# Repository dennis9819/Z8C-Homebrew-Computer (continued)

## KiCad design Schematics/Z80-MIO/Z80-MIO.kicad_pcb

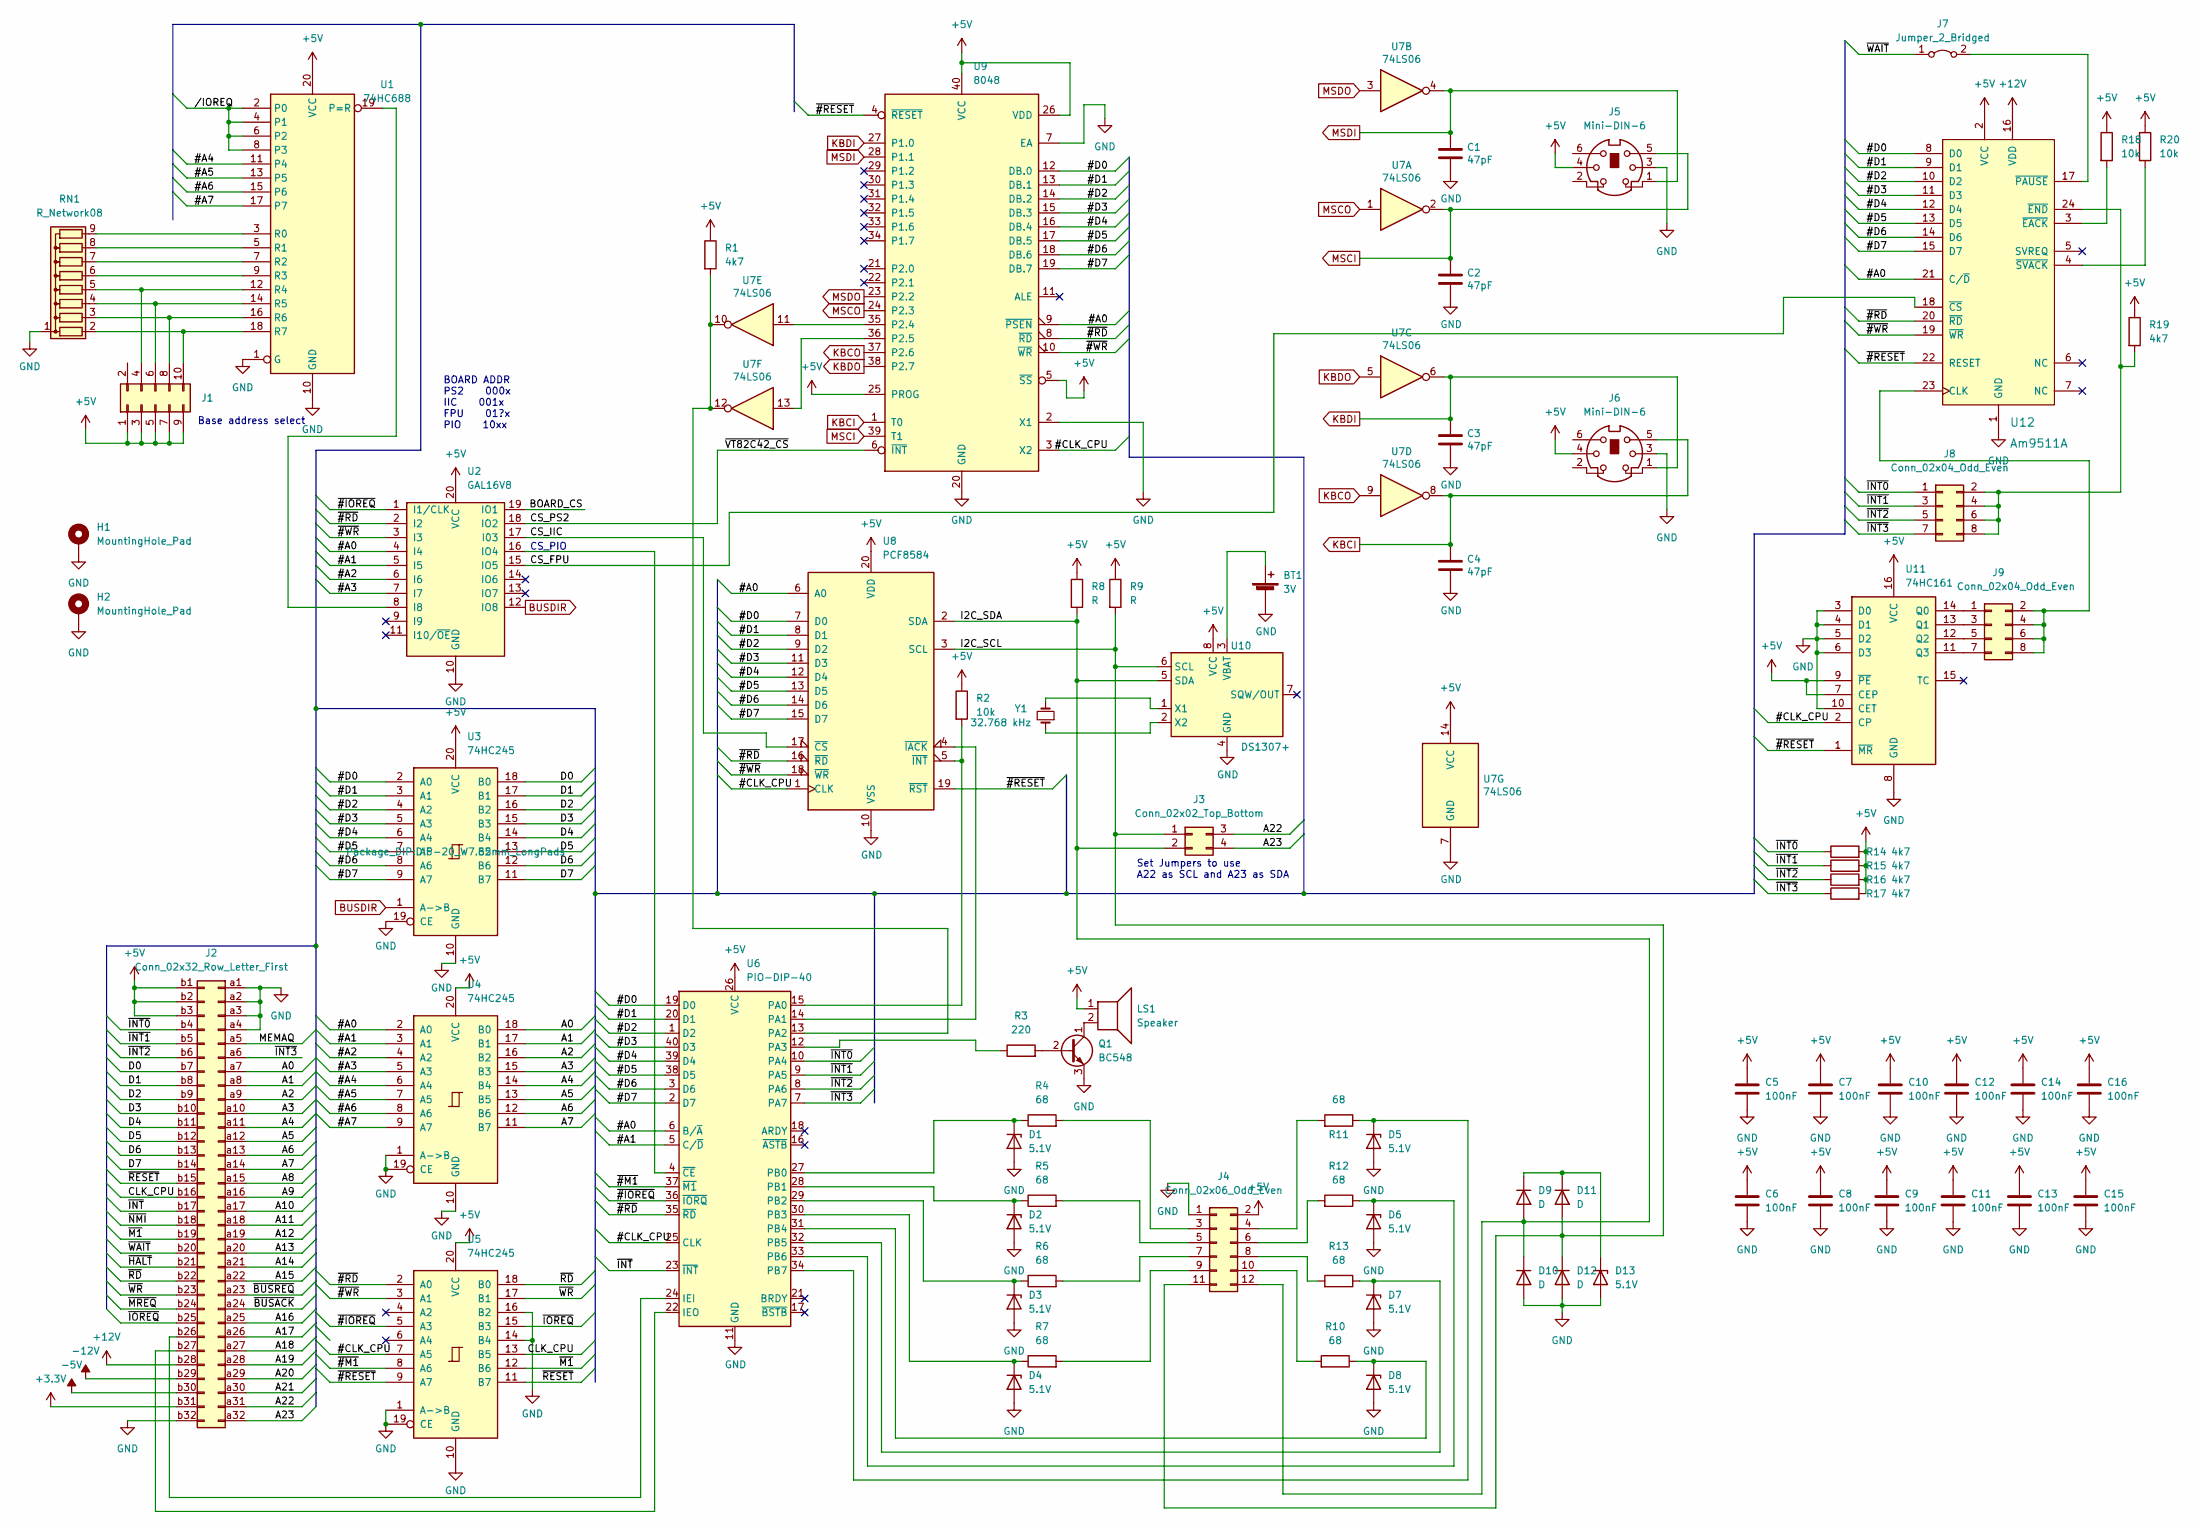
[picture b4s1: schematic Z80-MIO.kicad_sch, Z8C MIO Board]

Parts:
BT1: 3V; Battery_Holder_Coin_2032_BS-7
C1, C2, C3, C4: 47pF; C_Disc_D3.0mm_W2.0mm_P2.50mm
C5, C6, C7, C8, C9, C10, C11, C12, C13, C14, C15, C16: 100nF; C_Disc_D4.3mm_W1.9mm_P5.00mm
D1, D2, D3, D4, D5, D6, D7, D8, D13: 5.1V; D_DO-34_SOD68_P7.62mm_Horizontal
D9, D10, D11, D12: D; D_DO-34_SOD68_P7.62mm_Horizontal
H1, H2: MountingHole_Pad; MountingHole_3.2mm_M3_DIN965_Pad
J1: Conn_02x05_Odd_Even; PinHeader_2x05_P2.54mm_Vertical
J2: Conn_02x32_Row_Letter_First; DIN41612_Q_2x32_Male_Horizontal_THT
J3: Conn_02x02_Top_Bottom; PinHeader_2x02_P2.54mm_Vertical
J4: Conn_02x06_Odd_Even; IDC-Header_2x06_P2.54mm_Latch_Horizontal
J5, J6: Mini-DIN-6; PS2
J7: Jumper_2_Bridged; PinHeader_1x02_P2.54mm_Vertical
J8, J9: Conn_02x04_Odd_Even; PinHeader_2x04_P2.54mm_Vertical
LS1: Speaker; Piezo_Transducer_THT_PS1240P02BT
Q1: BC548; TO-92_Inline
R1, R14, R15, R16, R17, R19: 4k7; R_Axial_DIN0204_L3.6mm_D1.6mm_P7.62mm_Horizontal
R2, R18, R20: 10k; R_Axial_DIN0204_L3.6mm_D1.6mm_P7.62mm_Horizontal
R3: 220; R_Axial_DIN0204_L3.6mm_D1.6mm_P7.62mm_Horizontal
R4, R5, R6, R7, R10, R11, R12, R13: 68; R_Axial_DIN0204_L3.6mm_D1.6mm_P7.62mm_Horizontal
R8, R9: R; R_Axial_DIN0204_L3.6mm_D1.6mm_P7.62mm_Horizontal
RN1: R_Network08; R_Array_SIP9
U1: 74HC688; DIP-20_W7.62mm_LongPads
U2: GAL16V8; DIP-20_W7.62mm_LongPads
U3, U4, U5: 74HC245; DIP-20_W7.62mm_LongPads
U6: PIO-DIP-40; DIP-40_W15.24mm
U7: 74LS06; DIP-14_W7.62mm_Socket
U8: PCF8584; DIP-20_W7.62mm_LongPads
U9: 8048; DIP-40_W15.24mm_LongPads
U10: DS1307+; DIP-8_W7.62mm
U11: 74HC161; DIP-16_W7.62mm_LongPads
U12: Am9511A; DIP-24_W15.24mm_LongPads
Y1: 32.768 kHz; Crystal_AT310_D3.0mm_L10.0mm_Horizontal

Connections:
+3V3: J2.b31
+5V: C5.1, C6.1, C7.1, C8.1, C9.1, C10.1, C11.1, C12.1, C13.1, C14.1, C15.1, C16.1, J1.1, J1.3, J1.5, J1.7, J1.9, J2.b1, J2.b2, J2.b3, J4.2, J5.4, J6.4, LS1.1, R1.1, R2.1, R8.1, R9.1, R14.2, R15.2, R16.2, R17.2, R18.1, R19.1, R20.1, U1.20 (VCC), U2.20 (VCC), U3.20 (VCC), U4.20 (VCC), U5.20 (VCC), U6.26 (VCC), U7.14 (VCC), U8.20 (VDD), U9.5 (~SS), U9.25 (PROG), U9.26 (VDD), U9.40 (VCC), U10.8 (VCC), U11.7 (CEP), U11.9 (~PE), U11.16 (VCC), U12.2 (VCC)
+12V: J2.b28, U12.16 (VDD)
-5V: J2.b30
-12V: J2.b29
/#A0: U2.4 (I4), U4.2 (A0), U6.6 (B/~A), U8.6 (A0), U9.9 (~PSEN), U12.21 (C/~D)
/#A1: U2.5 (I5), U4.3 (A1), U6.5 (C/~D)
/#A2: U2.6 (I6), U4.4 (A2)
/#A3: U2.7 (I7), U4.5 (A3)
/#A4: U1.11 (P4), U4.6 (A4)
/#A5: U1.13 (P5), U4.7 (A5)
/#A6: U1.15 (P6), U4.8 (A6)
/#A7: U1.17 (P7), U4.9 (A7)
/#CLK_CPU: U5.7 (A5), U6.25 (CLK), U8.1 (CLK), U9.3 (X2), U11.2 (CP)
/#D0: U3.2 (A0), U6.19 (D0), U8.7 (D0), U9.12 (DB.0), U12.8 (D0)
/#D1: U3.3 (A1), U6.20 (D1), U8.8 (D1), U9.13 (DB.1), U12.9 (D1)
/#D2: U3.4 (A2), U6.1 (D2), U8.9 (D2), U9.14 (DB.2), U12.10 (D2)
/#D3: U3.5 (A3), U6.40 (D3), U8.11 (D3), U9.15 (DB.3), U12.11 (D3)
/#D4: U3.6 (A4), U6.39 (D4), U8.12 (D4), U9.16 (DB.4), U12.12 (D4)
/#D5: U3.7 (A5), U6.38 (D5), U8.13 (D5), U9.17 (DB.5), U12.13 (D5)
/#D6: U3.8 (A6), U6.3 (D6), U8.14 (D6), U9.18 (DB.6), U12.14 (D6)
/#D7: U3.9 (A7), U6.2 (D7), U8.15 (D7), U9.19 (DB.7), U12.15 (D7)
/A0: J2.a7, U4.18 (B0)
/A1: J2.a8, U4.17 (B1)
/A2: J2.a9, U4.16 (B2)
/A3: J2.a10, U4.15 (B3)
/A4: J2.a11, U4.14 (B4)
/A5: J2.a12, U4.13 (B5)
/A6: J2.a13, U4.12 (B6)
/A7: J2.a14, U4.11 (B7)
/A8: J2.a15
/A9: J2.a16
/A10: J2.a17
/A11: J2.a18
/A12: J2.a19
/A13: J2.a20
/A14: J2.a21
/A15: J2.a22
/A16: J2.a25
/A17: J2.a26
/A18: J2.a27
/A19: J2.a28
/A20: J2.a29
/A21: J2.a30
/A22: J2.a31, J3.3
/A23: J2.a32, J3.4
/BOARD_CS: U2.19 (IO1)
/CLK_CPU: J2.b16, U5.13 (B5)
/CS_FPU: U2.15 (IO5), U12.18 (~CS)
/CS_IIC: U2.17 (I03), U8.17 (~CS)
/CS_PS2: U2.18 (IO2), U9.6 (~INT)
/D0: J2.b7, U3.18 (B0)
/D1: J2.b8, U3.17 (B1)
/D2: J2.b9, U3.16 (B2)
/D3: J2.b10, U3.15 (B3)
/D4: J2.b11, U3.14 (B4)
/D5: J2.b12, U3.13 (B5)
/D6: J2.b13, U3.12 (B6)
/D7: J2.b14, U3.11 (B7)
/I2C_SCL: D11.2 (A), D12.1 (K), J3.1, J4.11, R9.2, U8.3 (SCL), U10.6 (SCL)
/I2C_SDA: D9.2 (A), D10.1 (K), J3.2, J4.12, R8.2, U8.2 (SDA), U10.5 (SDA)
/MEMAQ: J2.a5
//IOREQ: U1.2 (P0), U1.4 (P1), U1.6 (P2), U1.8 (P3)
/~#IOREQ: U2.1 (I1/CLK), U5.5 (A3), U6.36 (~IORQ)
/~#M1: U5.8 (A6), U6.37 (~M1)
/~#RD: U2.2 (I2), U5.2 (A0), U6.35 (~RD), U8.16 (~RD), U9.8 (~RD), U12.20 (~RD)
/~#RESET: U5.9 (A7), U8.19 (~RST), U9.4 (~RESET), U11.1 (~MR), U12.22 (RESET)
/~#WR: U2.3 (I3), U5.3 (A1), U8.18 (~WR), U9.10 (~WR), U12.19 (~WR)
/~BUSACK: J2.a24
/~BUSREQ: J2.a23
/~HALT: J2.b21
/~INT0: J2.b4, J8.1, R14.1, U6.10 (PA4)
/~INT1: J2.b5, J8.3, R15.1, U6.9 (PA5)
/~INT2: J2.b6, J8.5, R16.1, U6.8 (PA6)
/~INT3: J2.a6, J8.7, R17.1, U6.7 (PA7)
/~INT: J2.b17, U6.23 (~INT)
/~IOREQ: J2.b25, U5.15 (B3)
/~M1: J2.b19, U5.12 (B6)
/~MREQ: J2.b24
/~NMI: J2.b18
/~RD: J2.b22, U5.18 (B0)
/~RESET: J2.b15, U5.11 (B7)
/~WAIT: J2.b20, J7.1 (A)
/~WR: J2.b23, U5.17 (B1)
BUSDIR: U2.12 (IO8), U3.1 (A->B)
GND: BT1.neg, C1.2, C2.2, C3.2, C4.2, C5.2, C6.2, C7.2, C8.2, C9.2, C10.2, C11.2, C12.2, C13.2, C14.2, C15.2, C16.2, D1.2 (A), D2.2 (A), D3.2 (A), D4.2 (A), D5.2 (A), D6.2 (A), D7.2 (A), D8.2 (A), D10.2 (A), D12.2 (A), D13.2 (A), H1.1, H2.1, J2.a1, J2.a2, J2.a3, J2.a4, J2.b32, J4.1, J5.3, J6.3, Q1.3 (E), RN1.1 (common), U1.1 (G), U1.10 (GND), U2.10 (GND), U3.10 (GND), U3.19 (CE), U4.1 (A->B), U4.10 (GND), U4.19 (CE), U5.1 (A->B), U5.10 (GND), U5.14 (B4), U5.16 (B2), U5.19 (CE), U6.11 (GND), U7.7 (GND), U8.10 (VSS), U9.2 (X1), U9.7 (EA), U9.20 (GND), U10.4 (GND), U11.3 (D0), U11.4 (D1), U11.5 (D2), U11.6 (D3), U11.8 (GND), U11.10 (CET), U12.1 (GND)
KBCI: C4.1, J6.5, U7.8, U9.1 (T0)
KBCO: U7.9, U9.37 (P2.6)
KBDI: C3.1, J6.1, U7.6, U9.27 (P1.0)
KBDO: U7.5, U9.38 (P2.7)
MSCI: C2.1, J5.5, U7.2, U9.39 (T1)
MSCO: U7.1, U9.24 (P2.3)
MSDI: C1.1, J5.1, U7.4, U9.28 (P1.1)
MSDO: U7.3, U9.23 (P2.2)
unnamed: BT1.pos, U10.3 (VBAT)
unnamed: D1.1 (K), R4.1, U6.27 (PB0)
unnamed: D2.1 (K), R5.1, U6.28 (PB1)
unnamed: D3.1 (K), R6.1, U6.29 (PB2)
unnamed: D4.1 (K), R7.1, U6.30 (PB3)
unnamed: D5.1 (K), R11.1, U6.34 (PB7)
unnamed: D6.1 (K), R12.1, U6.33 (PB6)
unnamed: D7.1 (K), R13.1, U6.32 (PB5)
unnamed: D8.1 (K), R10.1, U6.31 (PB4)
unnamed: D9.1 (K), D11.1 (K), D13.1 (K)
unnamed: J1.4, RN1.5 (R4), U1.12 (R4)
unnamed: J1.6, RN1.4 (R3), U1.14 (R5)
unnamed: J1.8, RN1.3 (R2), U1.16 (R6)
unnamed: J1.10, RN1.2 (R1), U1.18 (R7)
unnamed: J2.b26, U6.24 (IEI)
unnamed: J2.b27, U6.22 (IEO)
unnamed: J4.3, R4.2
unnamed: J4.4, R11.2
unnamed: J4.5, R5.2
unnamed: J4.6, R12.2
unnamed: J4.7, R6.2
unnamed: J4.8, R13.2
unnamed: J4.9, R7.2
unnamed: J4.10, R10.2
unnamed: J7.2 (B), U12.17 (~PAUSE)
unnamed: J8.2, J8.4, J8.6, J8.8, R19.2, U12.24 (~END)
unnamed: J9.1, U11.14 (Q0)
unnamed: J9.2, J9.4, J9.6, J9.8, U12.23 (CLK)
unnamed: J9.3, U11.13 (Q1)
unnamed: J9.5, U11.12 (Q2)
unnamed: J9.7, U11.11 (Q3)
unnamed: LS1.2, Q1.1 (C)
unnamed: Q1.2 (B), R3.2
unnamed: R1.2, U6.13 (PA2), U7.10, U7.12
unnamed: R2.2, U6.15 (PA0), U8.5 (~INT)
unnamed: R3.1, U6.12 (PA3)
unnamed: R18.2, U12.3 (~EACK)
unnamed: R20.2, U12.4 (~SVACK)
unnamed: RN1.6 (R5), U1.9 (R3)
unnamed: RN1.7 (R6), U1.7 (R2)
unnamed: RN1.8 (R7), U1.5 (R1)
unnamed: RN1.9 (R8), U1.3 (R0)
unnamed: U1.19 (P=R), U2.8 (I8)
unnamed: U2.16 (IO4), U6.4 (~CE)
unnamed: U6.14 (PA1), U8.4 (~IACK)
unnamed: U7.11, U9.35 (P2.4)
unnamed: U7.13, U9.36 (P2.5)
unnamed: U10.1 (X1), Y1.2
unnamed: U10.2 (X2), Y1.1

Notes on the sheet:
CS_PIO
Base address select
Set Jumpers to use A22 as SCL and A23 as SDA
BOARD ADDR PS2 000x IIC 001x FPU 01?x PIO 10xx

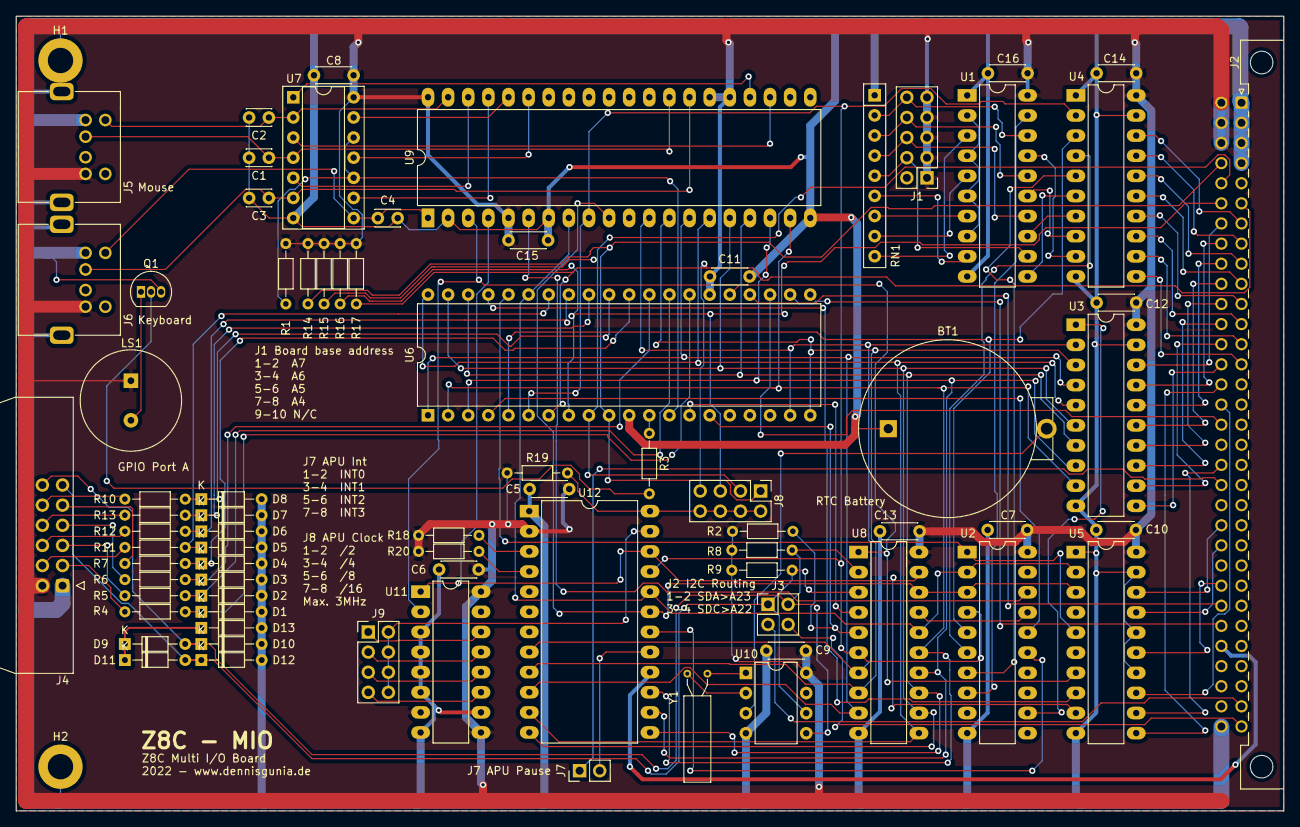
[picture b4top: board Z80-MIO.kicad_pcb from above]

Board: 2 copper layers, 160.0 x 100.3 mm, 77 parts (0 on the bottom side), 119 nets.
